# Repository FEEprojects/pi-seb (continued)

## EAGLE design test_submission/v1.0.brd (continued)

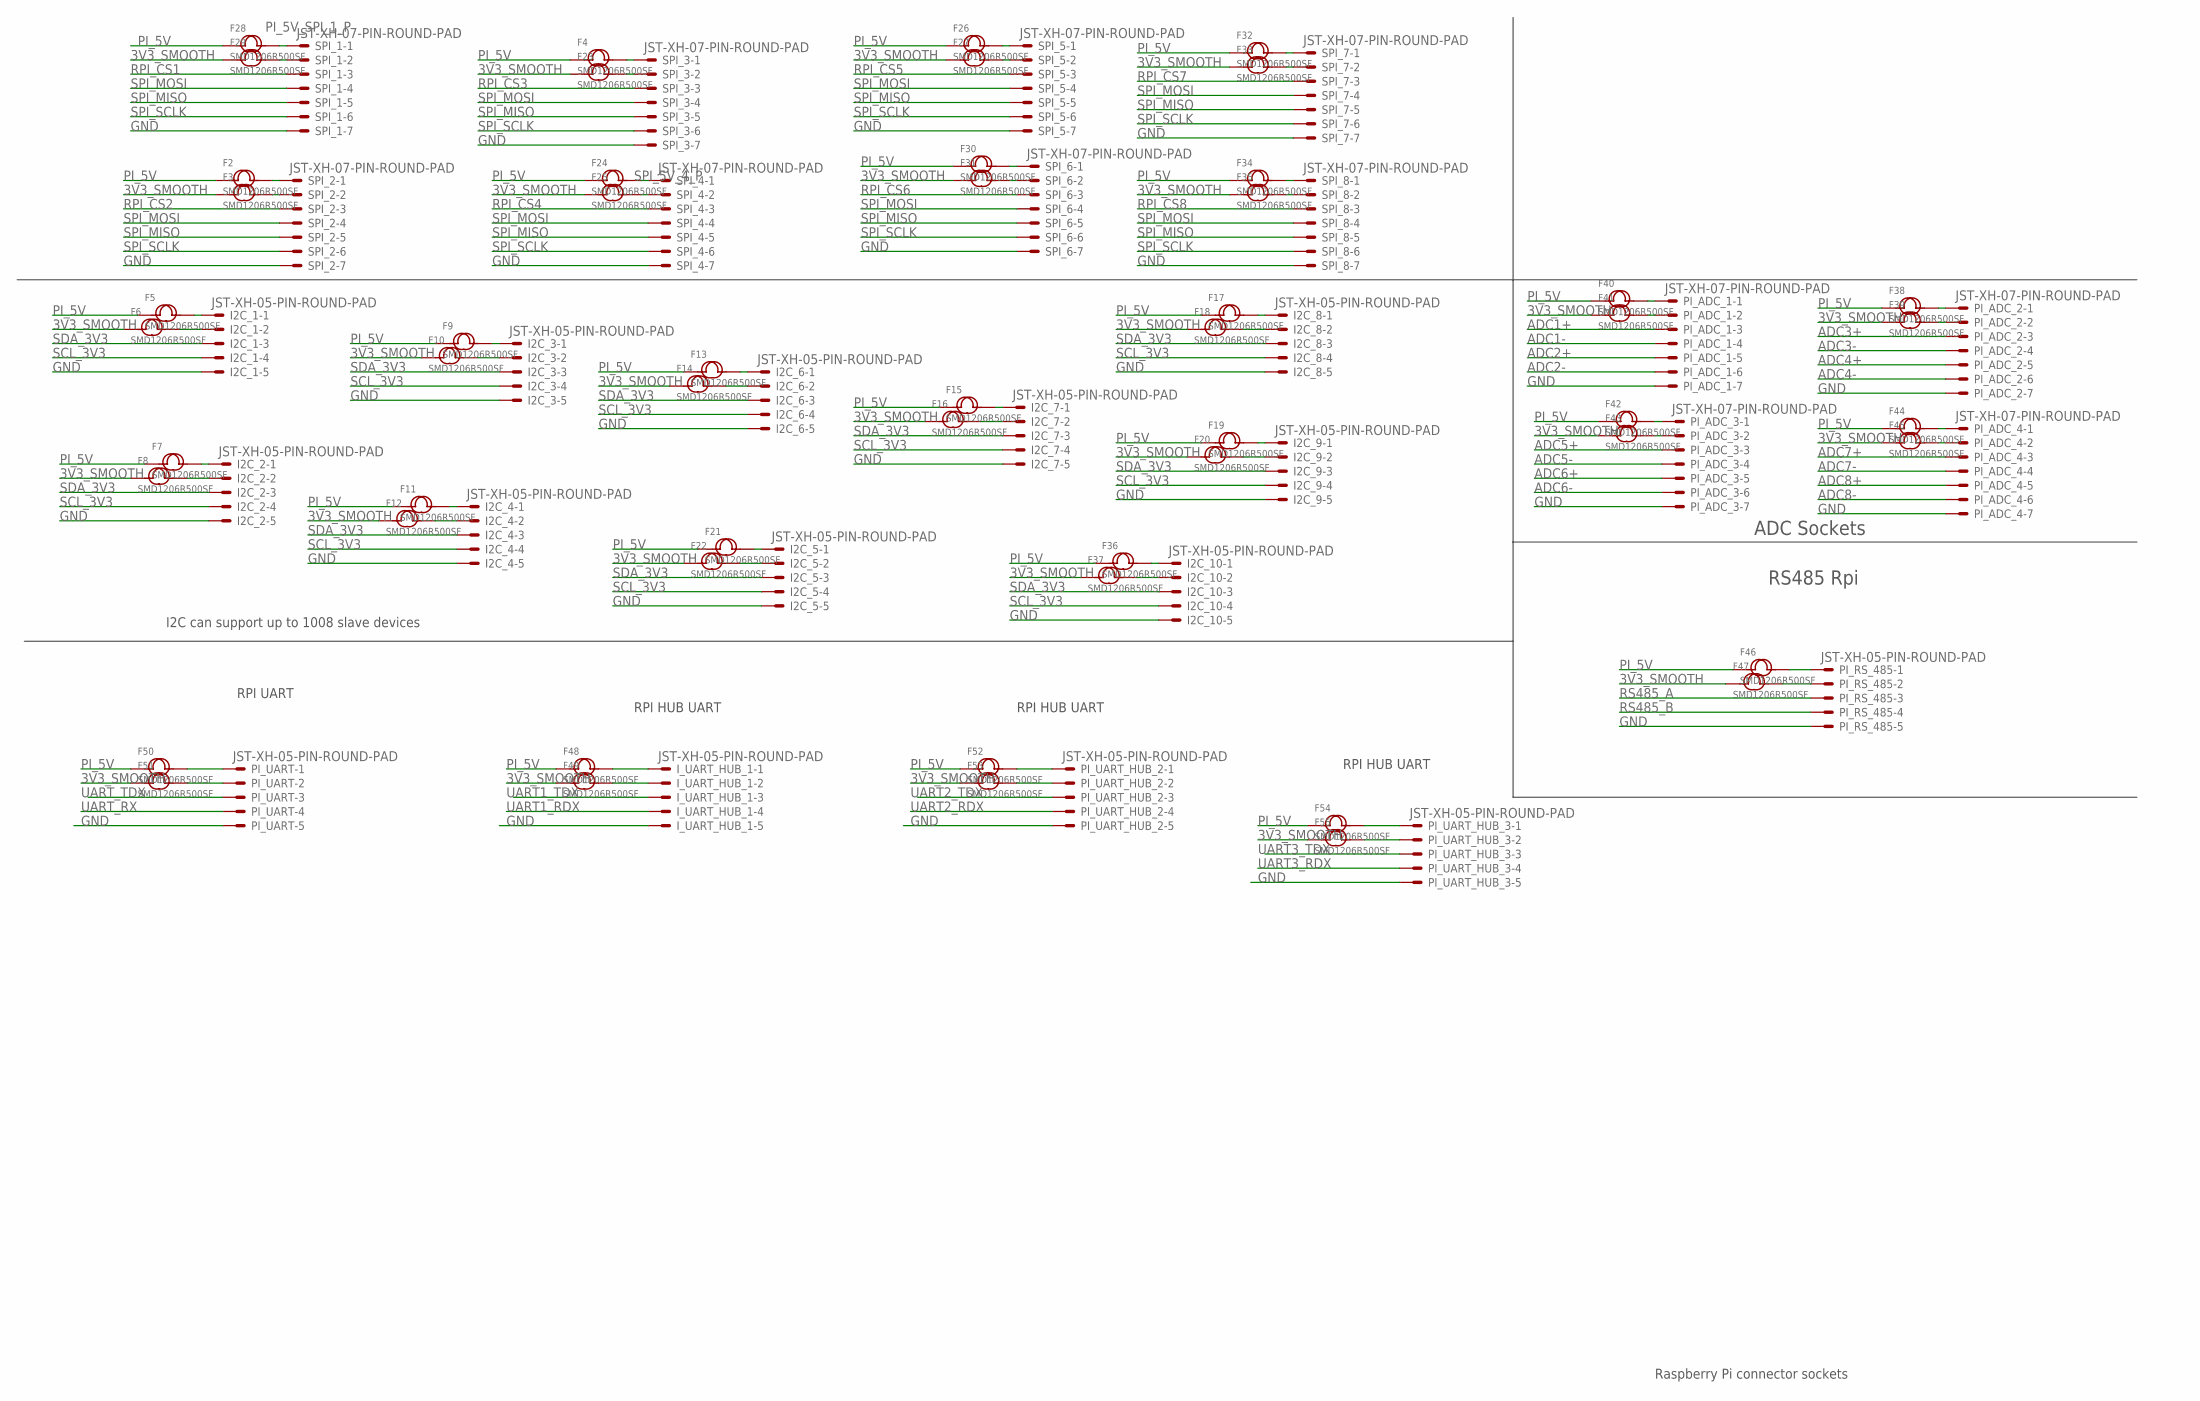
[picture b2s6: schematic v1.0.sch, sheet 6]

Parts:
F2, F3, F4, F5, F6, F7, F8, F9, F10, F11, F12, F13, F14, F15, F16, F17, F18, F19, F20, F21, F22, F23, F24, F25, F26, F27, F28, F29, F30, F31, F32, F33, F34, F35, F36, F37, F38, F39, F40, F41, F42, F43, F44, F45, F46, F47, F48, F49, F50, F51, F52, F53, F54, F55: SMD1206R500SF; F1206
I2C_1, I2C_2, I2C_3, I2C_4, I2C_5, I2C_6, I2C_7, I2C_8, I2C_9, I2C_10: JST-XH-05-PIN-ROUND-PAD; JST-XH-05-PACKAGE-ROUND-PAD
I_UART_HUB_1: JST-XH-05-PIN-ROUND-PAD; JST-XH-05-PACKAGE-ROUND-PAD
PI_ADC_1, PI_ADC_2, PI_ADC_3, PI_ADC_4: JST-XH-07-PIN-ROUND-PAD; JST-XH-07-PACKAGE-ROUND-PAD
PI_RS_485: JST-XH-05-PIN-ROUND-PAD; JST-XH-05-PACKAGE-ROUND-PAD
PI_UART: JST-XH-05-PIN-ROUND-PAD; JST-XH-05-PACKAGE-ROUND-PAD
PI_UART_HUB_2, PI_UART_HUB_3: JST-XH-05-PIN-ROUND-PAD; JST-XH-05-PACKAGE-ROUND-PAD
SPI_1, SPI_2, SPI_3, SPI_4, SPI_5, SPI_6, SPI_7, SPI_8: JST-XH-07-PIN-ROUND-PAD; JST-XH-07-PACKAGE-ROUND-PAD

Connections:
3V3_SMOOTH: F3.1, F6.1, F8.1, F10.1, F12.1, F14.1, F16.1, F18.1, F20.1, F22.1, F23.1, F25.1, F27.1, F29.1, F31.1, F33.1, F35.1, F37.1, F39.1, F41.1, F43.1, F45.1, F47.1, F49.1, F51.1, F53.1, F55.1; also elsewhere on the board
ADC1+: PI_ADC_1.3; also elsewhere on the board
ADC1-: PI_ADC_1.4; also elsewhere on the board
ADC2+: PI_ADC_1.5; also elsewhere on the board
ADC2-: PI_ADC_1.6; also elsewhere on the board
ADC3+: PI_ADC_2.3; also elsewhere on the board
ADC3-: PI_ADC_2.4; also elsewhere on the board
ADC4+: PI_ADC_2.5; also elsewhere on the board
ADC4-: PI_ADC_2.6; also elsewhere on the board
ADC5+: PI_ADC_3.3; also elsewhere on the board
ADC5-: PI_ADC_3.4; also elsewhere on the board
ADC6+: PI_ADC_3.5; also elsewhere on the board
ADC6-: PI_ADC_3.6; also elsewhere on the board
ADC7+: PI_ADC_4.3; also elsewhere on the board
ADC7-: PI_ADC_4.4; also elsewhere on the board
ADC8+: PI_ADC_4.5; also elsewhere on the board
ADC8-: PI_ADC_4.6; also elsewhere on the board
ADC_1_3V3_P: F41.2, PI_ADC_1.2
ADC_1_5V_P: F40.2, PI_ADC_1.1
ADC_2_3V3_P: F39.2, PI_ADC_2.2
ADC_2_5V_P: F38.2, PI_ADC_2.1
ADC_3_3V3_P: F43.2, PI_ADC_3.2
ADC_3_5V_P: F42.2, PI_ADC_3.1
ADC_4_3V3_P: F45.2, PI_ADC_4.2
ADC_4_5V_P: F44.2, PI_ADC_4.1
GND: I2C_1.5, I2C_2.5, I2C_3.5, I2C_4.5, I2C_5.5, I2C_6.5, I2C_7.5, I2C_8.5, I2C_9.5, I2C_10.5, I_UART_HUB_1.5, PI_ADC_1.7, PI_ADC_2.7, PI_ADC_3.7, PI_ADC_4.7, PI_RS_485.5, PI_UART.5, PI_UART_HUB_2.5, PI_UART_HUB_3.5, SPI_1.7, SPI_2.7, SPI_3.7, SPI_4.7, SPI_5.7, SPI_6.7, SPI_7.7, SPI_8.7; also elsewhere on the board
PI_5V: F2.1, F4.1, F5.1, F7.1, F9.1, F11.1, F13.1, F15.1, F17.1, F19.1, F21.1, F24.1, F26.1, F28.1, F30.1, F32.1, F34.1, F36.1, F38.1, F40.1, F42.1, F44.1, F46.1, F48.1, F50.1, F52.1, F54.1; also elsewhere on the board
PI_5V_SPI_1_P: F28.2, SPI_1.1
PI_I2C_2_5V_P: F9.2, I2C_3.1
PI_I2C_3V3_2_P: F10.2, I2C_3.2
PI_I2C_3V3_3: F6.2, I2C_1.2
PI_I2C_3V3_3_P: F8.2, I2C_2.2
PI_I2C_3V3_4_P: F12.2, I2C_4.2
PI_I2C_3V3_5_P: F14.2, I2C_6.2
PI_I2C_3V3_6_P: F22.2, I2C_5.2
PI_I2C_3V3_7_P: F16.2, I2C_7.2
PI_I2C_3V3_8_P: F18.2, I2C_8.2
PI_I2C_3V3_9_P: F20.2, I2C_9.2
PI_I2C_3V3_10_P: F37.2, I2C_10.2
PI_I2C_5V_3_P: F7.2, I2C_2.1
PI_I2C_5V_4_P: F11.2, I2C_4.1
PI_I2C_5V_5_P: F13.2, I2C_6.1
PI_I2C_5V_6_P: F21.2, I2C_5.1
PI_I2C_5V_7_P: F15.2, I2C_7.1
PI_I2C_5V_8_P: F17.2, I2C_8.1
PI_I2C_5V_9_P: F19.2, I2C_9.1
PI_I2C_5V_10_P: F36.2, I2C_10.1
PI_I2C_5V_P: F5.2, I2C_1.1
PI_RS485_3V3_P: F47.2, PI_RS_485.2
PI_RS485_5V_P: F46.2, PI_RS_485.1
PI_SPI_3V3_1_P: F29.2, SPI_1.2
PI_SPI_5V_2_P: F2.2, SPI_2.1
PI_UART_3V3_P: F51.2, PI_UART.2
PI_UART_5V_P: F50.2, PI_UART.1
PI_UART_HUB_1_3V3_P: F49.2, I_UART_HUB_1.2
PI_UART_HUB_1_5V_P: F48.2, I_UART_HUB_1.1
PI_UART_HUB_2_3V3_P: F53.2, PI_UART_HUB_2.2
PI_UART_HUB_2_5V_P: F52.2, PI_UART_HUB_2.1
RPI_CS1: SPI_1.3; also elsewhere on the board
RPI_CS2: SPI_2.3; also elsewhere on the board
RPI_CS3: SPI_3.3; also elsewhere on the board
RPI_CS4: SPI_4.3; also elsewhere on the board
RPI_CS5: SPI_5.3; also elsewhere on the board
RPI_CS6: SPI_6.3; also elsewhere on the board
RPI_CS7: SPI_7.3; also elsewhere on the board
RPI_CS8: SPI_8.3; also elsewhere on the board
RS485_A: PI_RS_485.3; also elsewhere on the board
RS485_B: PI_RS_485.4; also elsewhere on the board
SCL_3V3: I2C_1.4, I2C_2.4, I2C_3.4, I2C_4.4, I2C_5.4, I2C_6.4, I2C_7.4, I2C_8.4, I2C_9.4, I2C_10.4; also elsewhere on the board
SDA_3V3: I2C_1.3, I2C_2.3, I2C_3.3, I2C_4.3, I2C_5.3, I2C_6.3, I2C_7.3, I2C_8.3, I2C_9.3, I2C_10.3; also elsewhere on the board
SPI_3V3_2_P: F3.2, SPI_2.2
SPI_3V3_3_P: F23.2, SPI_3.2
SPI_3V3_4_P: F25.2, SPI_4.2
SPI_3V3_5_P: F27.2, SPI_5.2
SPI_3V3_6_P: F31.2, SPI_6.2
SPI_3V3_7_P: F33.2, SPI_7.2
SPI_3V3_8_P: F35.2, SPI_8.2
SPI_5V_3_P: F4.2, SPI_3.1
SPI_5V_4_P: F24.2, SPI_4.1
SPI_5V_5_P: F26.2, SPI_5.1
SPI_5V_6_P: F30.2, SPI_6.1
SPI_5V_7_P: F32.2, SPI_7.1
SPI_5V_8_P: F34.2, SPI_8.1
SPI_MISO: SPI_1.5, SPI_2.5, SPI_3.5, SPI_4.5, SPI_5.5, SPI_6.5, SPI_7.5, SPI_8.5; also elsewhere on the board
SPI_MOSI: SPI_1.4, SPI_2.4, SPI_3.4, SPI_4.4, SPI_5.4, SPI_6.4, SPI_7.4, SPI_8.4; also elsewhere on the board
SPI_SCLK: SPI_1.6, SPI_2.6, SPI_3.6, SPI_4.6, SPI_5.6, SPI_6.6, SPI_7.6, SPI_8.6; also elsewhere on the board
UART1_RDX: I_UART_HUB_1.4; also elsewhere on the board
UART1_TDX: I_UART_HUB_1.3; also elsewhere on the board
UART2_RDX: PI_UART_HUB_2.4; also elsewhere on the board
UART2_TDX: PI_UART_HUB_2.3; also elsewhere on the board
UART3_RDX: PI_UART_HUB_3.4; also elsewhere on the board
UART3_TDX: PI_UART_HUB_3.3; also elsewhere on the board
UART_HUB_3_3V3_P: F55.2, PI_UART_HUB_3.2
UART_RX: PI_UART.4; also elsewhere on the board
UART_TDX: PI_UART.3; also elsewhere on the board
UART_USB_HUB_3_5V: F54.2, PI_UART_HUB_3.1

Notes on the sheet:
Raspberry Pi connector sockets
I2C can support up to 1008 slave devices
ADC Sockets
RS485 Rpi
RPI UART
RPI HUB UART

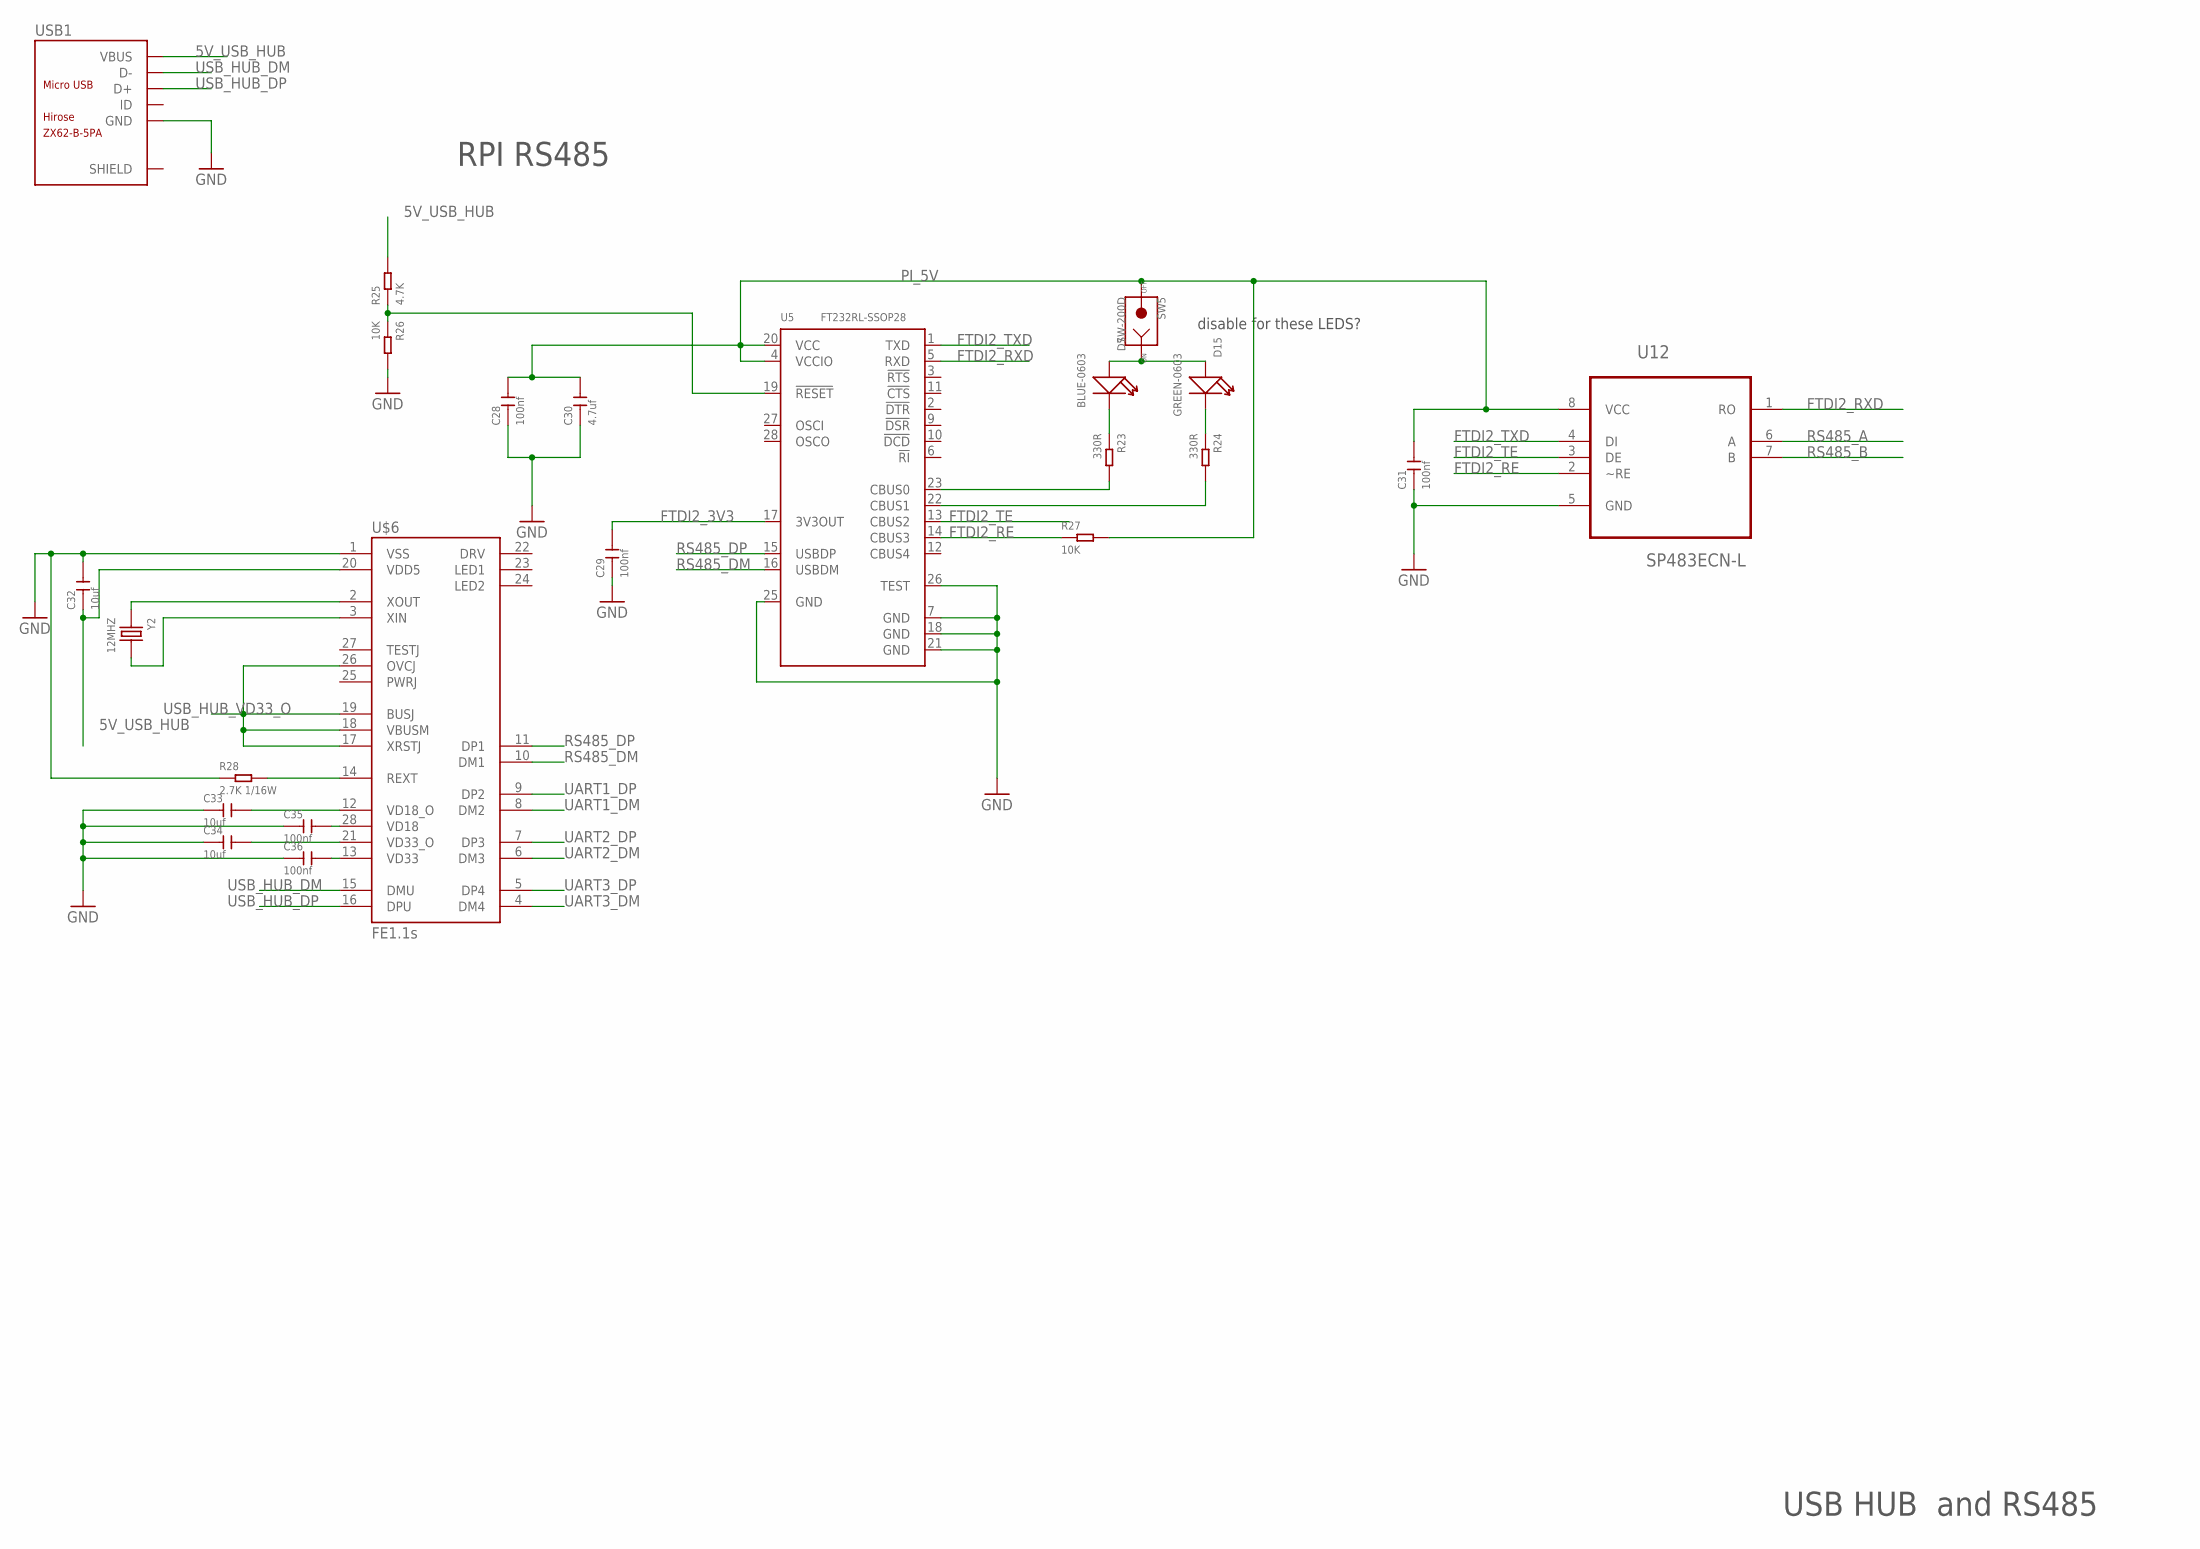
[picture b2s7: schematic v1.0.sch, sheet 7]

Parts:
C28, C29, C35, C36: 100nf; C0603
C30: 4.7uf; C0603
C31: 100nf; C0805
C32, C33, C34: 10uf; C0805
D7: BLUE-0603; LED-0603
D15: GREEN-0603; LED-0603
R23, R24: 330R; R0603
R25: 4.7K; R0603
R26, R27: 10K; R0603
R28: 2.7K 1/16W; R0402
SW5: SW-200D; SW2-12.7-12.0X3.6X3.6MM
U5: FT232RL-SSOP28; SSOP28-0.65-10.2X5.2MM
U12: SP483ECN-L; SOIC127P600X175-8N
U$6: FE1.1S; FE1.1S_SSOP-28
USB1: ZX62-B-5PA; MICRO-USB5+6P-SMD-0.65-AB
Y2: 12MHZ; X2-SMD-5.0X3.2X1.3MM

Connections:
5V_USB_HUB: C32.1, R25.2, U$6.20 (VDD5), USB1.1 (VBUS); also elsewhere on the board
FTDI2_3V3: C29.2, U5.17 (3V3OUT)
FTDI2_CBUS1: R23.2, U5.23 (CBUS0)
FTDI2_RE: R27.1, U5.14 (CBUS3), U12.2 (~RE)
FTDI2_RXD: U5.5 (RXD), U12.1 (RO)
FTDI2_TE: U5.13 (CBUS2), U12.3 (DE)
FTDI2_TXD: U5.1 (TXD), U12.4 (DI)
FTID2_CBUS2: R24.2, U5.22 (CBUS1)
GND: C28.1, C29.1, C30.1, C31.1, C32.2, C33.1, C34.1, C35.1, C36.1, R26.2, R28.1, U5.7 (GND), U5.18 (GND), U5.21 (GND), U5.25 (GND), U5.26 (TEST), U12.5 (GND), U$6.1 (VSS), USB1.5 (GND); also elsewhere on the board
unnamed: D7.+, D15.+, SW5.1
unnamed: D7.-, R23.1
unnamed: D15.-, R24.1
unnamed: R25.1, R26.1, U5.19 (!RESET)
unnamed: U$6.2 (XOUT), Y2.1
unnamed: U$6.3 (XIN), Y2.2
unnamed: R28.2, U$6.14 (REXT)
unnamed: C35.2, U$6.28 (VD18)
unnamed: C36.2, U$6.13 (VD33)
unnamed: C34.2, U$6.21 (VD33_O)
unnamed: C33.2, U$6.12 (VD18_O)
PI_5V: C28.2, C30.2, C31.2, R27.2, SW5.2, U5.4 (VCCIO), U5.20 (VCC), U12.8 (VCC); also elsewhere on the board
RS485_A: U12.6 (A); also elsewhere on the board
RS485_B: U12.7 (B); also elsewhere on the board
RS485_DM: U5.16 (USBDM), U$6.10 (DM1)
RS485_DP: U5.15 (USBDP), U$6.11 (DP1)
UART1_DM: U$6.8 (DM2); also elsewhere on the board
UART1_DP: U$6.9 (DP2); also elsewhere on the board
UART2_DM: U$6.6 (DM3); also elsewhere on the board
UART2_DP: U$6.7 (DP3); also elsewhere on the board
UART3_DM: U$6.4 (DM4); also elsewhere on the board
UART3_DP: U$6.5 (DP4); also elsewhere on the board
USB_HUB_DM: U$6.15 (DMU), USB1.2 (D-)
USB_HUB_DP: U$6.16 (DPU), USB1.3 (D+)
USB_HUB_VD33_O: U$6.17 (XRSTJ), U$6.18 (VBUSM), U$6.19 (BUSJ), U$6.26 (OVCJ)

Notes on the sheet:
RPI RS485
disable for these LEDS?
USB HUB and RS485

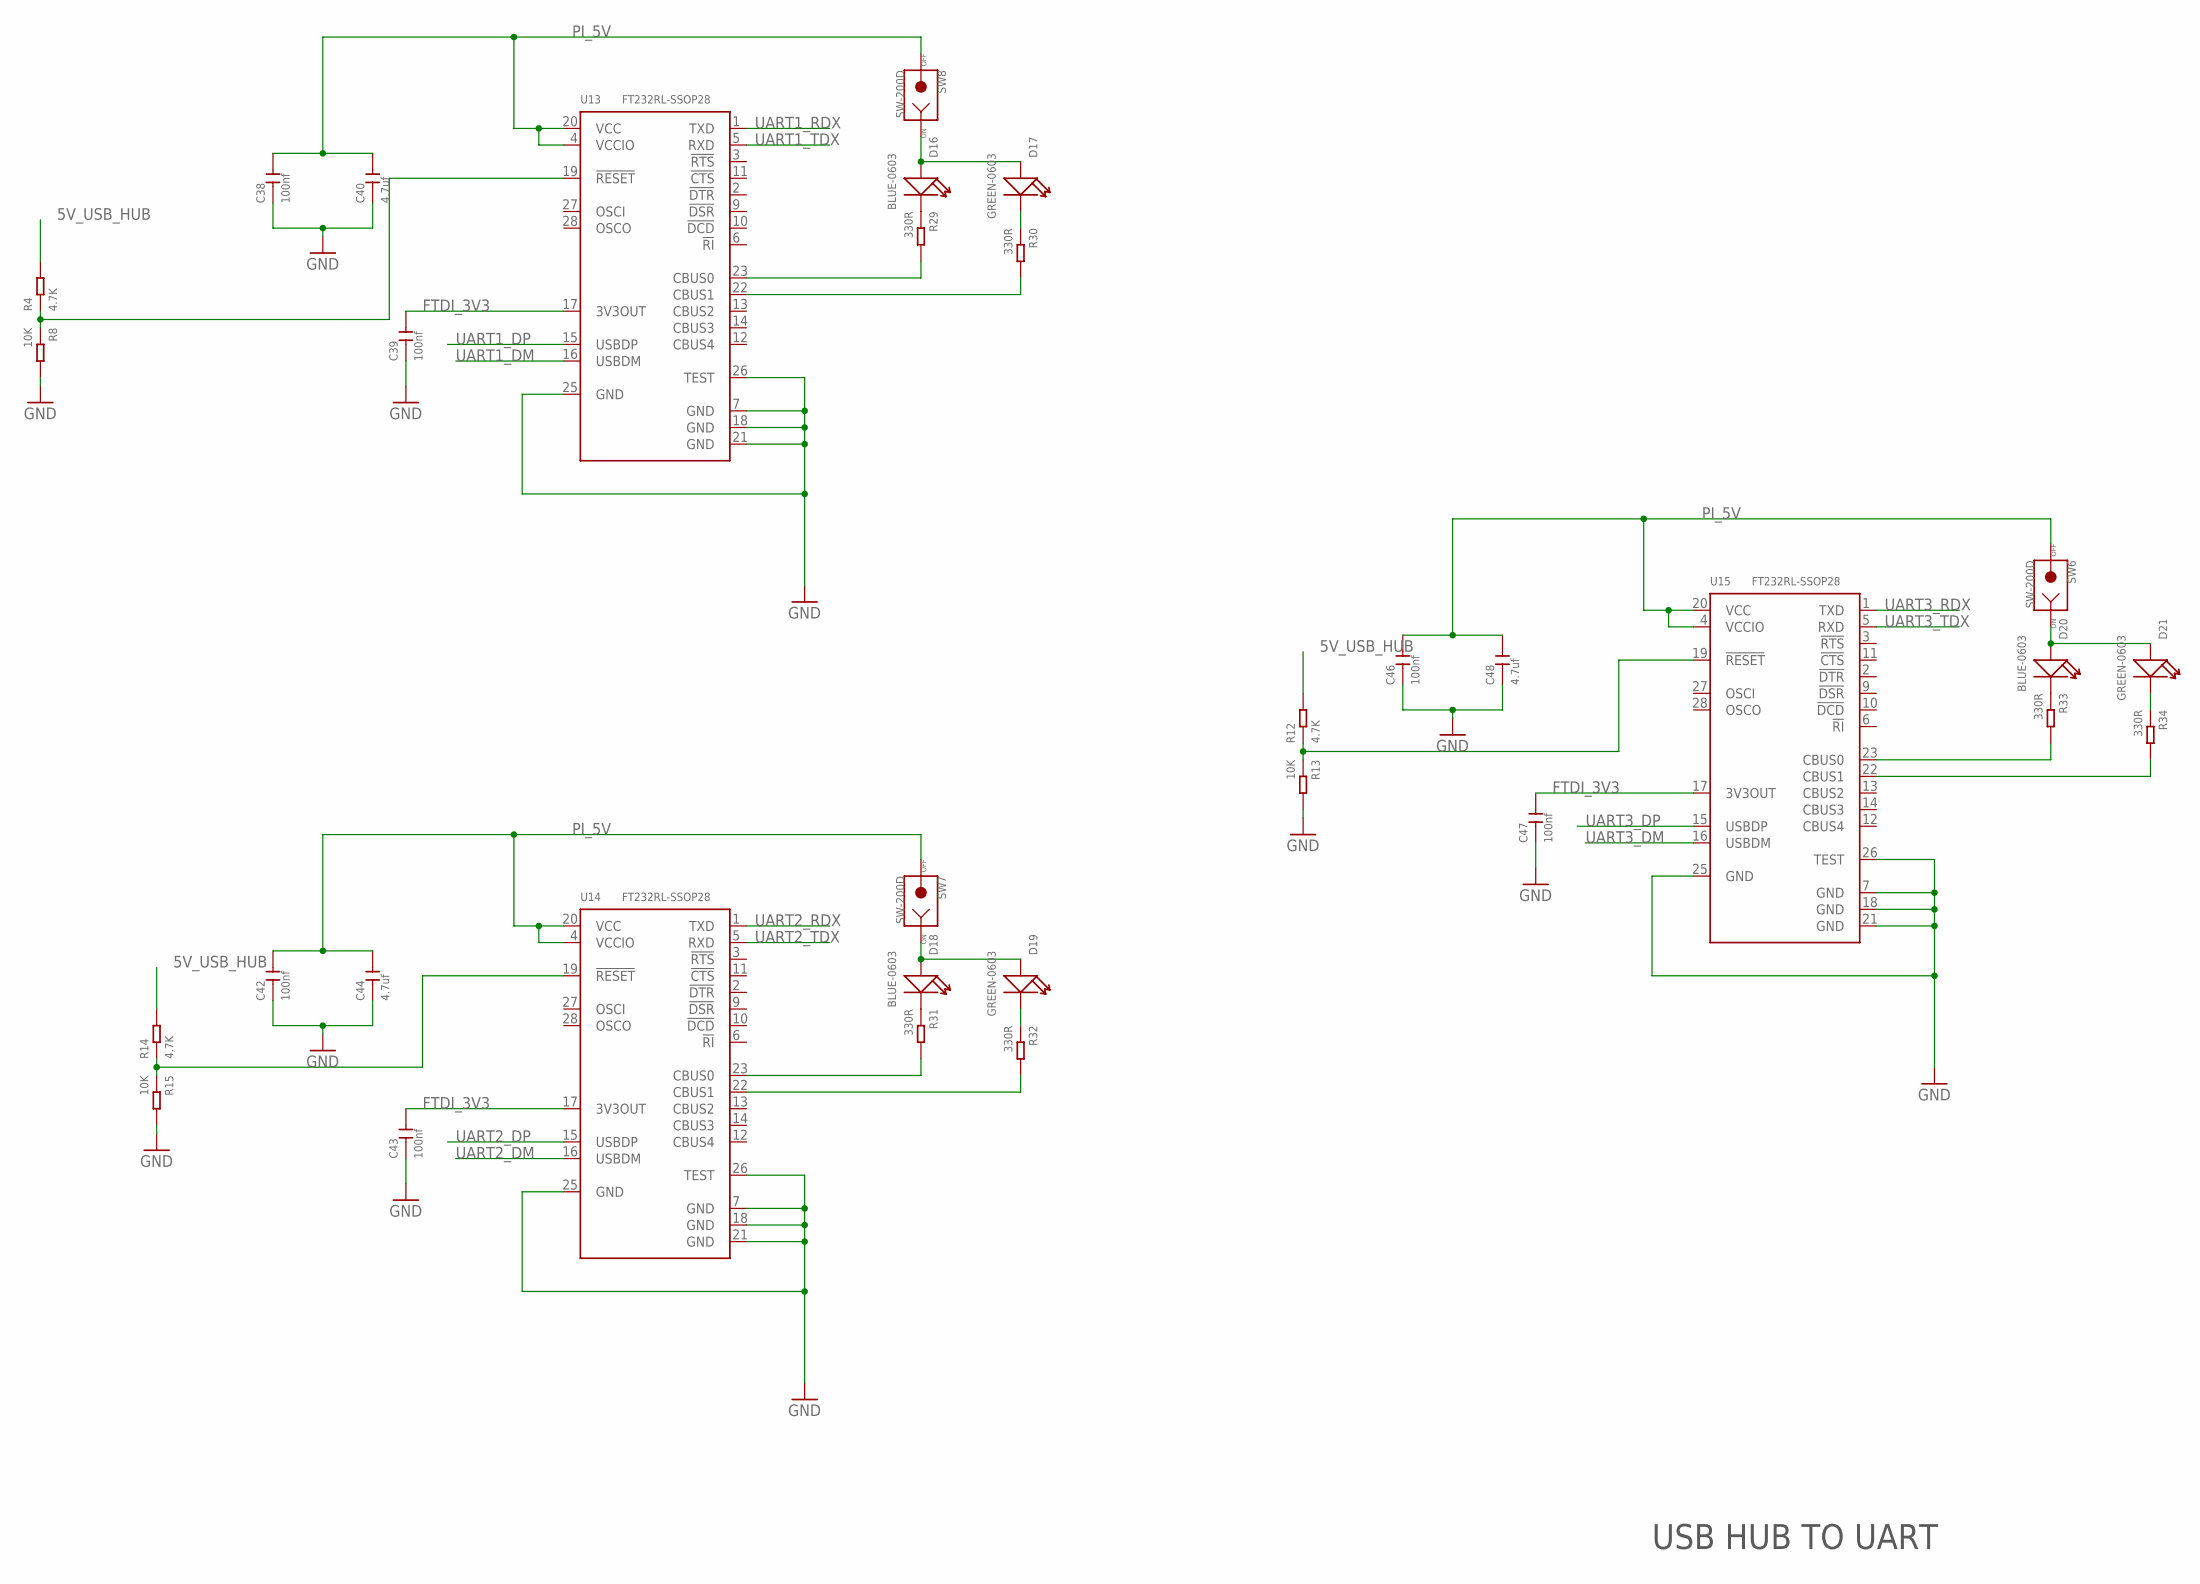
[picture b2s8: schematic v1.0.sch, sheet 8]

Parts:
C38, C39, C42, C43, C46, C47: 100nf; C0603
C40, C44, C48: 4.7uf; C0603
D16, D18, D20: BLUE-0603; LED-0603
D17, D19, D21: GREEN-0603; LED-0603
R4, R12, R14: 4.7K; R0603
R8, R13, R15: 10K; R0603
R29, R30, R31, R32, R33, R34: 330R; R0603
SW6, SW7, SW8: SW-200D; SW2-12.7-12.0X3.6X3.6MM
U13, U14, U15: FT232RL-SSOP28; SSOP28-0.65-10.2X5.2MM

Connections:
5V_USB_HUB: R4.2, R12.2, R14.2; also elsewhere on the board
FTDI_3V3: C39.2, C43.2, C47.2, U13.17 (3V3OUT), U14.17 (3V3OUT), U15.17 (3V3OUT); also elsewhere on the board
GND: C38.1, C39.1, C40.1, C42.1, C43.1, C44.1, C46.1, C47.1, C48.1, R8.2, R13.2, R15.2, U13.7 (GND), U13.18 (GND), U13.21 (GND), U13.25 (GND), U13.26 (TEST), U14.7 (GND), U14.18 (GND), U14.21 (GND), U14.25 (GND), U14.26 (TEST), U15.7 (GND), U15.18 (GND), U15.21 (GND), U15.25 (GND), U15.26 (TEST); also elsewhere on the board
unnamed: R4.1, R8.1, U13.19 (!RESET)
unnamed: R12.1, R13.1, U15.19 (!RESET)
unnamed: R14.1, R15.1, U14.19 (!RESET)
unnamed: D20.+, D21.+, SW6.1
unnamed: D18.+, D19.+, SW7.1
unnamed: D16.+, D17.+, SW8.1
unnamed: D16.-, R29.1
unnamed: D17.-, R30.1
unnamed: R29.2, U13.23 (CBUS0)
unnamed: R30.2, U13.22 (CBUS1)
unnamed: D18.-, R31.1
unnamed: D19.-, R32.1
unnamed: R31.2, U14.23 (CBUS0)
unnamed: R32.2, U14.22 (CBUS1)
unnamed: D20.-, R33.1
unnamed: D21.-, R34.1
unnamed: R33.2, U15.23 (CBUS0)
unnamed: R34.2, U15.22 (CBUS1)
PI_5V: C38.2, C40.2, C42.2, C44.2, C46.2, C48.2, SW6.2, SW7.2, SW8.2, U13.4 (VCCIO), U13.20 (VCC), U14.4 (VCCIO), U14.20 (VCC), U15.4 (VCCIO), U15.20 (VCC); also elsewhere on the board
UART1_DM: U13.16 (USBDM); also elsewhere on the board
UART1_DP: U13.15 (USBDP); also elsewhere on the board
UART1_RDX: U13.1 (TXD); also elsewhere on the board
UART1_TDX: U13.5 (RXD); also elsewhere on the board
UART2_DM: U14.16 (USBDM); also elsewhere on the board
UART2_DP: U14.15 (USBDP); also elsewhere on the board
UART2_RDX: U14.1 (TXD); also elsewhere on the board
UART2_TDX: U14.5 (RXD); also elsewhere on the board
UART3_DM: U15.16 (USBDM); also elsewhere on the board
UART3_DP: U15.15 (USBDP); also elsewhere on the board
UART3_RDX: U15.1 (TXD); also elsewhere on the board
UART3_TDX: U15.5 (RXD); also elsewhere on the board

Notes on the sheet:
USB HUB TO UART

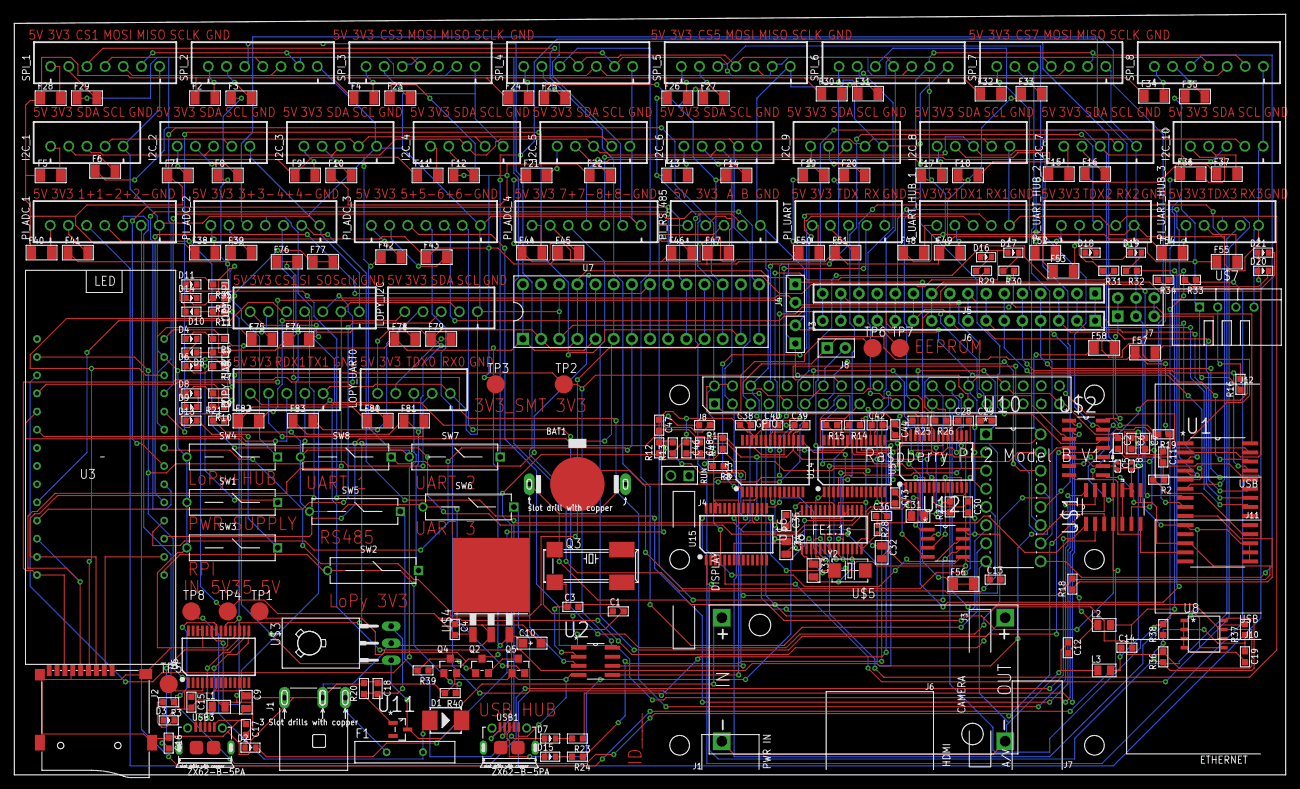
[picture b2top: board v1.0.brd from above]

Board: 2 copper layers, 177.8 x 106.3 mm, 251 parts (0 on the bottom side), 239 nets.

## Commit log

2017-06-02 started everything from scratch using opl library
2017-06-02 schematic
2017-06-05 libraries
2017-06-05 datasheets
2017-06-05 Remove prior versions
2017-06-05 updated gitignore
2017-06-05 remove .DS file
2017-06-05 As worked on together
2017-06-05 datasheet and SPI CS expander
2017-06-05 SPI CS expander
2017-06-05 added SPI CS expander on it's own page
2017-06-06 gitignore changed for $ filenames
2017-06-06 added power circuit
2017-06-06 .gitignore works
2017-06-07 Fix ignore for library files as well
2017-06-07 now includes part number in filename
2017-06-07 General tidying, PSU mods, and pycom library created and added
2017-06-07 tried adc library - pins do not show on device
2017-06-08 DC&DC from seeed library
2017-06-08 seeed dc-dc library finished RTC added
2017-06-08 added crystal for RTC
2017-06-08 pycom
2017-06-08 LDO for 5V
2017-06-08 very minor tweaks
2017-06-08 added pycom accessories
2017-06-08 pycom USB
2017-06-08 USB to FT23
2017-06-11 lopy FTDI and SD card socket
2017-06-11 RPI SPI, I2C and UART sockets
2017-06-11 polyfuse on Vin
2017-06-12 Git ignore updated to remove .b$$ file
2017-06-12 Various tidying
2017-06-12 lopy connectors
2017-06-12 lopy the rest of the connectors
2017-06-12 RS485
2017-06-12 datasheet
2017-06-12 rtc crystals changed pi now power controller bypass for ldo rs485 driver
2017-06-13 now correct version from yesterdays modifications
2017-06-13 replaced with PI_5V and 3V3_SMOOTH where relevant
2017-06-13 adc sockets
2017-06-13 changed back to +5V - has LDO on it - and added RS485 socket
2017-06-13 zener diode
2017-06-13 polyfuses
2017-06-13 start of poly fuse tidy
2017-06-13 I think I am done?
2017-06-13 overvoltage
2017-06-13 Remove random osx file
2017-06-13 Some tidying
2017-06-13 tidy sockets
2017-06-13 mcp23017 socket
2017-06-14 finally thyristor - to check the library and grid
2017-06-14 changing ldo
2017-06-15 corrections in
2017-06-16 corrections
2017-06-18 eeprom and USB hub + UART
2017-06-19 changed pins on sockets to have ground at the end
2017-06-19 version printed, submitted to Steven
2017-06-19 solving errors
2017-06-20 starting board layout
2017-06-20 board start
2017-06-20 board arrangement
2017-06-21 started double checking board position against schematics
2017-06-21 board done
2017-06-22 added temperature sensor and started labelling the board sockets
2017-06-22 names and board labels
2017-06-22 seeed submission - still looking for .ulp file to create bom
2017-06-23 adding rs232 level converter
2017-06-23 level converter added
2017-06-23 board done after adding the level converter
2017-06-23 added the mounting holes, need to tidy the board
2017-06-23 added corrections on first 2 pages
2017-06-23 changes names for 3v3 out for ftdi chip
2017-06-23 fist changes
2017-06-25 all the corrections are in, I am making a another check
2017-06-25 added corrections and had a check
2017-06-26 General pendantry of tidying and ERC etc
2017-06-26 Clustering things ready for PCB layout
2017-06-27 Added correct LM2596 datasheet, removed the wrong one.
2017-06-27 remove datasheets from root
2017-06-27 added tab to schematic
2017-06-27 before autoroute attempt
2017-06-27 Most of the board laid out
2017-06-28 All components now placed
2017-06-28 Added datasheet for replacement quartz crystal
2017-06-28 Board layout potentially complete - just needs a name now
2017-06-29 Added datasheets for headers used
2017-06-30 Pi control of LoPy reset added Pi & lopy uart0 connected
2017-07-03 Switches changed for toggle as opposed to push FETs added for Pi -> lopy control lines
2017-07-03 Now has 2 TTL serial ports
2017-07-04 As submitted
2017-07-12 Part placement file generated
2017-08-02 Add the v1 schematic and board into the folder
2017-08-02 Start of mods for V2
2017-08-03 moved some test pads around
2017-08-04 More work on fixing bugs
2017-08-04 fixed name of pycom pin 12 signal track
2017-08-08 More updates to fix issues and start of v2 BOM
2017-08-09 More updates, and verifing of current state of BOM
2017-08-10 Lopy reset and bootloader now on port expander
2017-08-10 Start of connector / fuse rationalisation
2017-08-10 More rearranging
2017-08-10 Updated BOM to match Eagle data. Added Seeed BOM.
2017-08-10 V2 laid out
2017-08-11 Removed two fuses, as per the final version
2017-08-11 Added missing pricing information
2017-08-11 RTC changed to one that doesn't rely on external crystal
2017-08-11 Added final few parts
2017-08-11 More layout changes
2017-08-11 More layout tweaking
2017-08-11 Added UART 0-ohms and UART Pi 1 header
2017-08-11 Fixed quantities
2017-08-11 More minor layout tweaks
2017-08-13 Added custom PiSEB logo
    Logo imported using this tutorial: https://learn.sparkfun.com/tutorials/importing-custom-images-into-eagle/all
2017-09-11 added the schematic and board into v2 folder
2019-01-15 remove unnecessary files
2019-01-21 Add readme
2019-01-21 Add License
2019-01-21 Add DOI badge
